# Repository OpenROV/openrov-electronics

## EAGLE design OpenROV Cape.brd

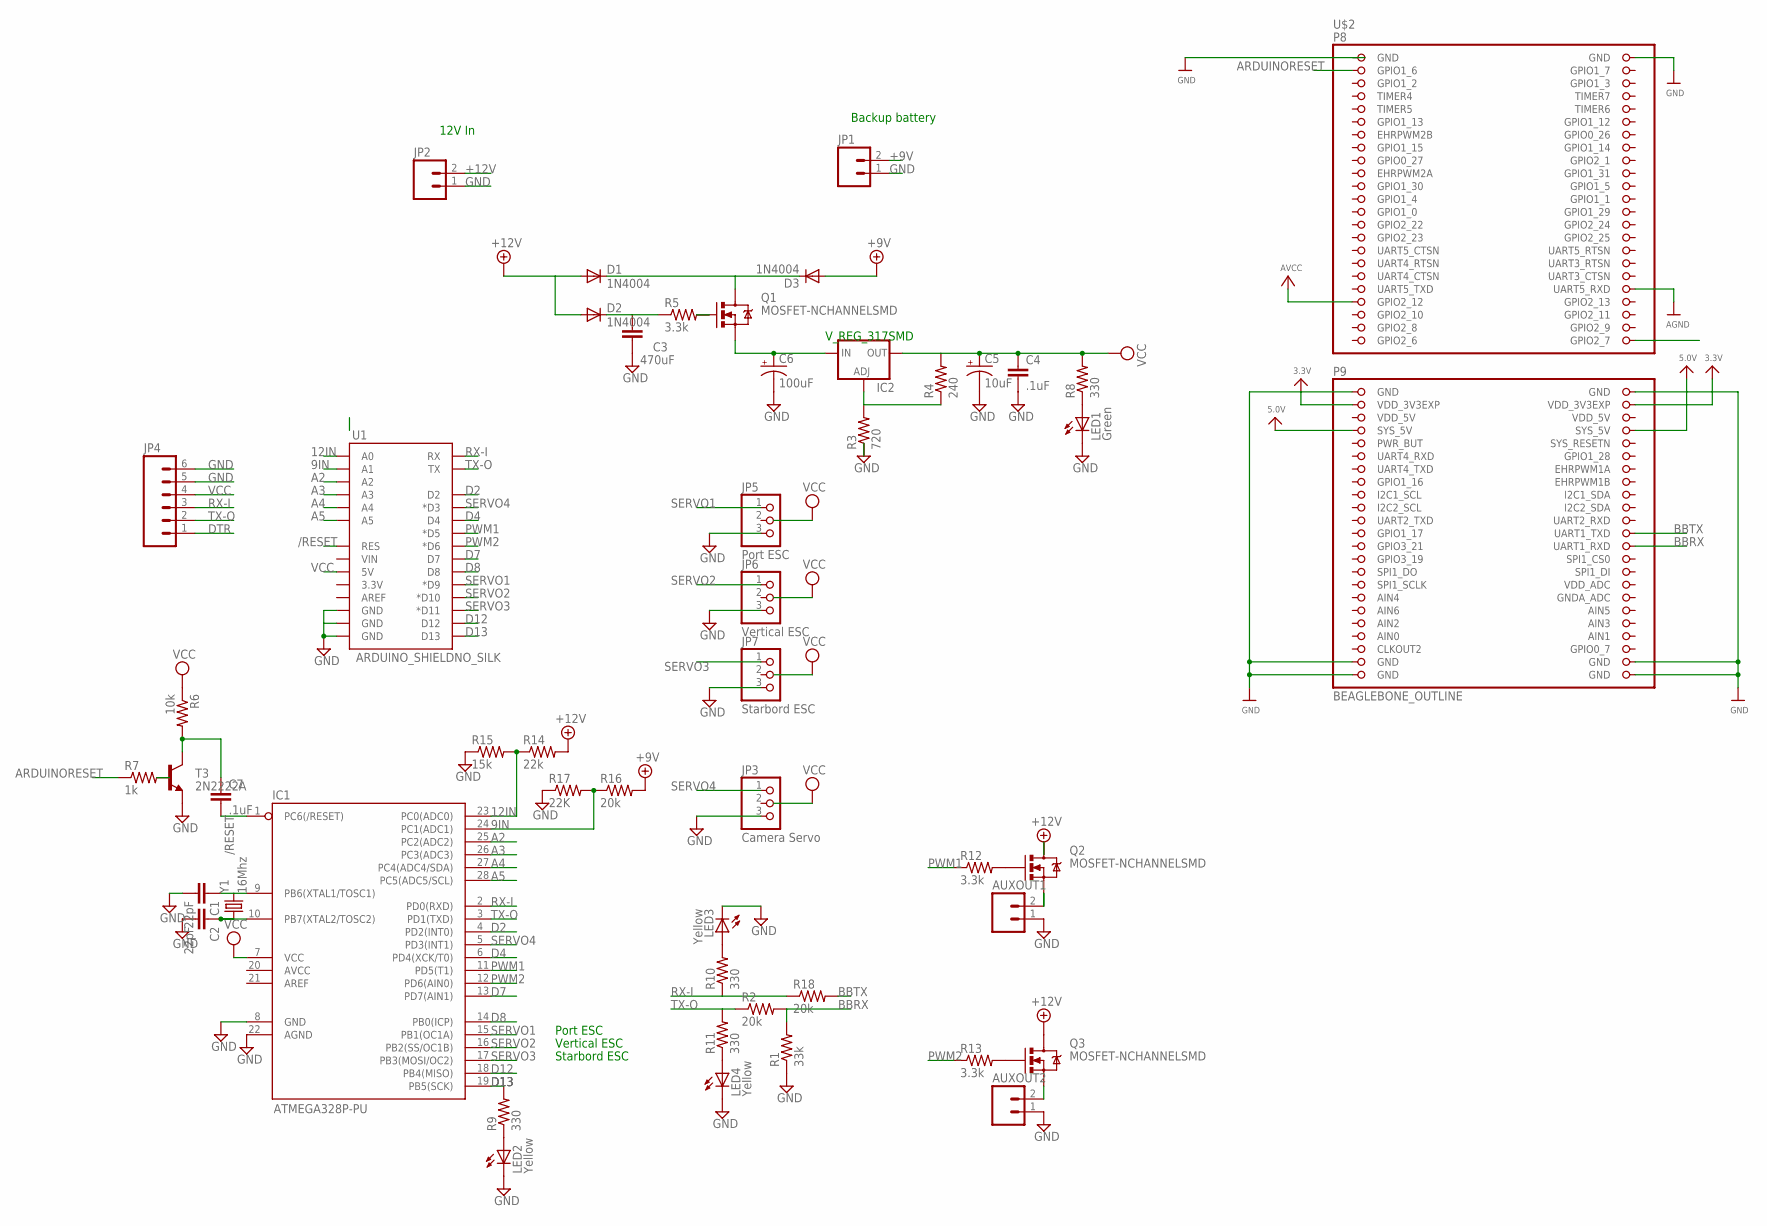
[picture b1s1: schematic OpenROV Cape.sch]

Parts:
AUXOUT1, AUXOUT2: M02PTH; 1X02
C1, C2: 22pF; 0805
C3: 470uF; 0805
C4, C7: .1uF; 0805
C5: 10uF; EIA3216
C6: 100uF; EIA3216
D1, D2, D3: 1N4004; SMA-DIODE
IC1: ATMEGA328P-PU; DIL28-3
IC2: V_REG_317SMD; SOT223
JP1, JP2: M02PTH; 1X02
JP3: Camera Servo; 1X03
JP4: M06SIP; 1X06
JP5: Port ESC; 1X03
JP6: Vertical ESC; 1X03
JP7: Starbord ESC; 1X03
LED1: Green; LED-1206
LED2, LED3, LED4: Yellow; LED-1206
Q1, Q2, Q3: MOSFET-NCHANNELSMD; SOT23-3
R1: 33k; 0805
R2, R16, R18: 20k; 0805
R3: 720; 0805
R4: 240; 0805
R5, R12, R13: 3.3k; 0805
R6: 10k; 0805
R7: 1k; 0805
R8, R9, R10, R11: 330; 0805
R14: 22k; 0805
R15: 15k; 0805
R17: 22K; 0805
T3: 2N2222A; SOT23
U1: ARDUINO_SHIELDNO_SILK; DUEMILANOVE_VIAS
U$2: BEAGLEBONE_OUTLINE; BEAGLEBONE_SHIELD
Y1: 16Mhz; HC49US

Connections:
3.3V: U$2.49 (VDD_3V3EXP), U$2.50 (VDD_3V3EXP)
5.0V: U$2.53 (SYS_5V), U$2.54 (SYS_5V)
9IN: IC1.24 (PC1(ADC1)), R16.1, R17.2, U1.A1
12IN: IC1.23 (PC0(ADC0)), R14.1, R15.2, U1.A0
+9V: D3.A, JP1.2, R16.2
+12V: D1.A, D2.A, JP2.2, Q2.3 (D), Q3.3 (D), R14.2
/RESET: C7.1, R6.2, T3.3 (C), U1.RES
A2: IC1.25 (PC2(ADC2)), U1.A2
A3: IC1.26 (PC3(ADC3)), U1.A3
A4: IC1.27 (PC4(ADC4/SDA)), U1.A4
A5: IC1.28 (PC5(ADC5/SCL)), U1.A5
AGND: U$2.38 (UART5_RXD)
AIN0: U$2.85 (AIN0)
AIN3: U$2.84 (AIN3)
ARDUINORESET: R7.1, U$2.3 (GPIO1_6)
AVCC: U$2.39 (GPIO2_12)
BBRX: R1.2, R2.2, U$2.72 (UART1_RXD)
BBTX: R18.2, U$2.70 (UART1_TXD)
D2: IC1.4 (PD2(INT0)), U1.D2
D4: IC1.6 (PD4(XCK/T0)), U1.D4
D7: IC1.13 (PD7(AIN1)), U1.D7
D8: IC1.14 (PB0(ICP)), U1.D8
D12: IC1.18 (PB4(MISO)), U1.D12
D13: IC1.19 (PB5(SCK)), R9.2, U1.D13
DTR: JP4.1
GND: AUXOUT1.1, AUXOUT2.1, C1.2, C2.2, C3.2, C4.2, C5.C (-), C6.C (-), IC1.22 (AGND), JP1.1, JP2.1, JP3.3, JP4.5, JP4.6, JP5.3, JP6.3, JP7.3, LED1.C, LED2.C, LED3.C, LED4.C, R1.1, R3.1, R15.1, R17.1, T3.2 (E), U1.GND@0 (GND), U1.GND@1 (GND), U1.GND@2 (GND), U$2.1 (GND), U$2.2 (GND), U$2.47 (GND), U$2.48 (GND), U$2.89 (GND), U$2.90 (GND), U$2.91 (GND), U$2.92 (GND)
GPIO1_7: U$2.4 (GPIO1_7)
GPIO2_6: U$2.45 (GPIO2_6)
GPIO2_8: U$2.43 (GPIO2_8)
GPIO2_9: U$2.44 (GPIO2_9)
GPIO2_11: U$2.42 (GPIO2_11)
unnamed: LED3.A, R10.2
unnamed: C7.2, IC1.1 (PC6(/RESET))
unnamed: R7.2, T3.1 (B)
unnamed: IC2.1 (ADJ), R3.2, R4.1
unnamed: LED1.A, R8.1
unnamed: LED2.A, R9.1
unnamed: LED4.A, R11.1
unnamed: AUXOUT1.2, Q2.2 (S)
unnamed: Q2.1 (G), R12.2
unnamed: AUXOUT2.2, Q3.2 (S)
unnamed: Q3.1 (G), R13.2
unnamed: C2.1, IC1.10 (PB7(XTAL2/TOSC2)), Y1.1
unnamed: C1.1, IC1.9 (PB6(XTAL1/TOSC1)), Y1.2
unnamed: C3.1, D2.C, R5.1
unnamed: Q1.1 (G), R5.2
unnamed: D1.C, D3.C, Q1.3 (D)
unnamed: C6.A (+), IC2.3 (IN), Q1.2 (S)
PWM1: IC1.11 (PD5(T1)), R12.1, U1.D5 (*D5)
PWM2: IC1.12 (PD6(AIN0)), R13.1, U1.D6 (*D6)
RX-I: IC1.2 (PD0(RXD)), JP4.3, R10.1, R18.1, U1.RX
SERVO1: IC1.15 (PB1(OC1A)), JP5.1, U1.D9 (*D9)
SERVO2: IC1.16 (PB2(SS/OC1B)), JP6.1, U1.D10 (*D10)
SERVO3: IC1.17 (PB3(MOSI/OC2)), JP7.1, U1.D11 (*D11)
SERVO4: IC1.5 (PD3(INT1)), JP3.1, U1.D3 (*D3)
TX-O: IC1.3 (PD1(TXD)), JP4.2, R2.1, R11.2, U1.TX
VCC: C4.1, C5.A (+), IC1.7 (VCC), IC2.2 (OUT), JP4.4, R4.2, R6.1, R8.2, U1.5V
VDD_5V: U$2.51 (VDD_5V), U$2.52 (VDD_5V)

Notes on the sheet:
Port ESC
Vertical ESC
Starbord ESC
Backup battery
12V In
V_REG_317SMD

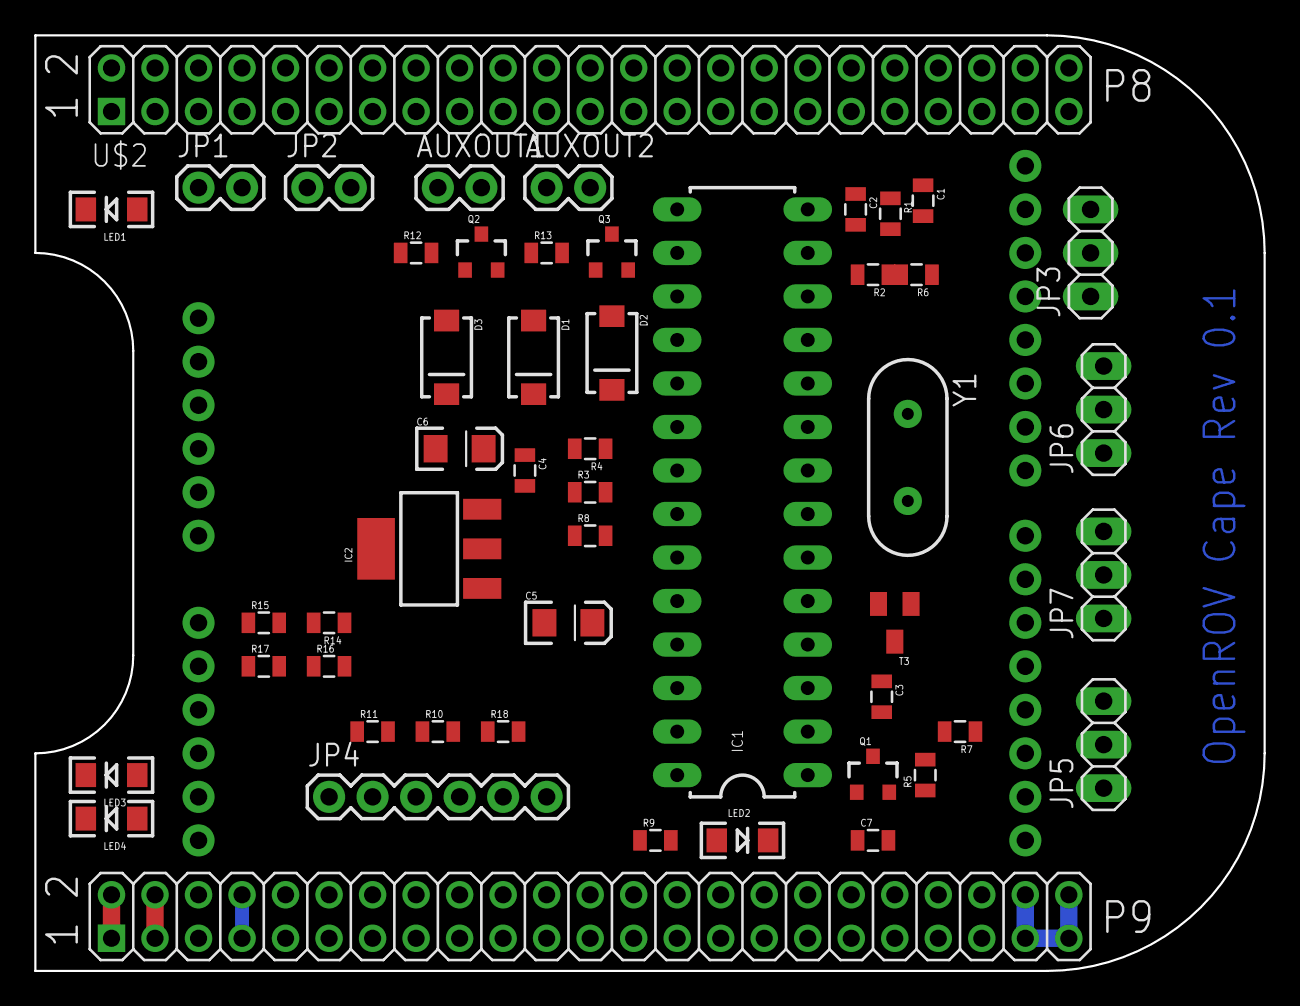
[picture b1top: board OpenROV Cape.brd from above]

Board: 2 copper layers, 71.8 x 54.6 mm, 50 parts (0 on the bottom side), 48 nets.

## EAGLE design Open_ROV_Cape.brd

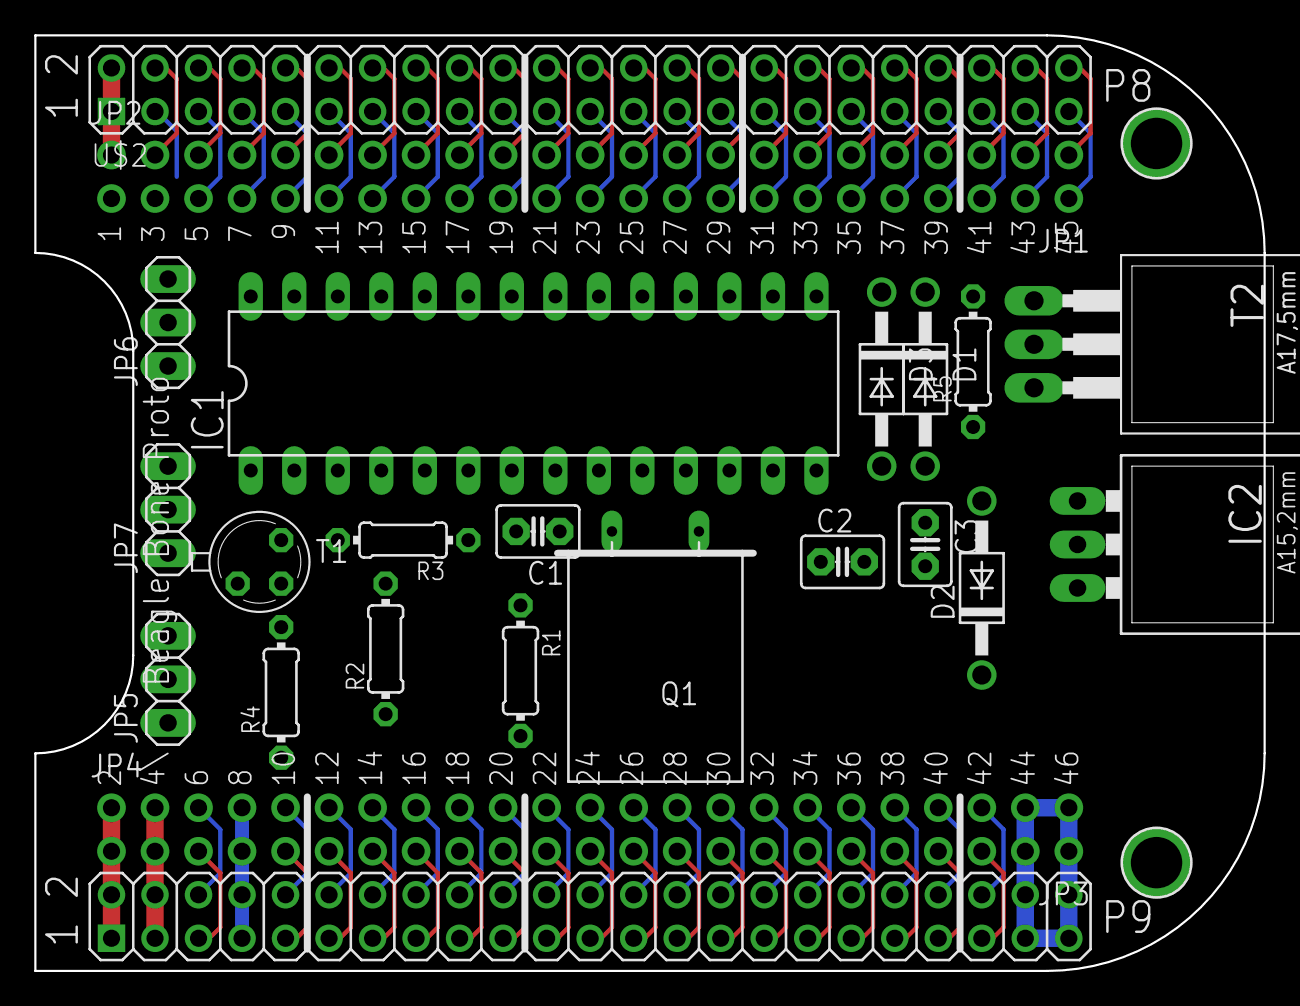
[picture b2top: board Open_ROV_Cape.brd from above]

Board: 2 copper layers, 71.8 x 54.6 mm, 26 parts (0 on the bottom side), 95 nets.

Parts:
C1, C2, C3: C2.5-3
D1, D2, D3: 1N4004; DO41-10
IC1: DIL28-4
IC2: 78XXL
JP1, JP2, JP3, JP4: 1X23_ROUND_70MIL
JP5, JP6, JP7: 1X03
Q1: Q
R1, R2, R3, R4, R5: 0204/7
T1: 2N2222; TO18
T2: TIP122; TO220
U$2: BEAGLEBONE_OUTLINE; BEAGLEBONE_SHIELD
U$22, U$23: MOUNTINGHOLE3.0THIN; MOUNTINGHOLE_3.0_PLATEDTHIN

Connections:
3.3V: JP3.22, JP4.2, U$2.49, U$2.50
5.0V: JP3.20, JP4.4, U$2.53, U$2.54
+12V: D1.A, D2.A
AGND: JP2.19, U$2.38
AVCC: JP1.4, U$2.39
GND: C1.2, C2.2, C3.2, IC1.8, IC1.22, IC2.GND, JP1.23, JP2.1, JP3.1, JP3.2, JP3.23, JP4.1, JP4.22, JP4.23, JP5.3, JP6.3, JP7.3, R1.1, T1.1, U$2.1, U$2.2, U$2.47, U$2.48, U$2.89, U$2.90, U$2.91, U$2.92
unnamed: IC1.1, R3.2, T1.3
unnamed: R4.2, T1.2
unnamed: JP1.20, U$2.7
unnamed: JP1.19, U$2.9
unnamed: JP1.18, U$2.11
unnamed: JP1.17, U$2.13
unnamed: JP1.16, U$2.15
unnamed: JP1.15, U$2.17
unnamed: JP1.14, U$2.19
unnamed: JP1.13, U$2.21
unnamed: JP1.12, U$2.23
unnamed: JP1.11, U$2.25
unnamed: JP1.10, U$2.27
unnamed: JP1.9, U$2.29
unnamed: JP1.8, U$2.31
unnamed: JP1.7, U$2.33
unnamed: JP1.6, U$2.35
unnamed: JP1.5, U$2.37
unnamed: JP1.3, U$2.41
unnamed: JP1.2, U$2.43
unnamed: JP1.1, U$2.45
unnamed: C2.1, IC1.10, Q1.1
unnamed: C1.1, IC1.9, Q1.2
unnamed: JP2.4, U$2.8
unnamed: JP2.5, U$2.10
unnamed: JP2.6, U$2.12
unnamed: JP2.7, U$2.14
unnamed: JP2.8, U$2.16
unnamed: JP2.9, U$2.18
unnamed: JP2.10, U$2.20
unnamed: JP2.11, U$2.22
unnamed: JP2.12, U$2.24
unnamed: JP2.13, U$2.26
unnamed: JP2.14, U$2.28
unnamed: JP2.15, U$2.30
unnamed: JP2.16, U$2.32
unnamed: JP2.17, U$2.34
unnamed: JP2.18, U$2.36
unnamed: JP2.20, U$2.40
unnamed: JP2.21, U$2.42
unnamed: JP2.22, U$2.44
unnamed: JP2.23, U$2.46
unnamed: JP1.22, U$2.3
unnamed: JP1.21, U$2.5
unnamed: JP3.21, U$2.51
unnamed: JP2.2, U$2.4
unnamed: JP3.19, U$2.55
unnamed: JP3.18, U$2.57
unnamed: JP3.17, U$2.59
unnamed: JP3.16, U$2.61
unnamed: JP3.15, U$2.63
unnamed: JP3.14, U$2.65
unnamed: JP3.13, U$2.67
unnamed: JP3.12, U$2.69
unnamed: JP3.11, U$2.71
unnamed: JP3.10, U$2.73
unnamed: JP3.9, U$2.75
unnamed: JP3.8, U$2.77
unnamed: JP3.7, U$2.79
unnamed: JP3.6, U$2.81
unnamed: JP3.5, U$2.83
unnamed: JP3.4, U$2.85
unnamed: JP3.3, U$2.87
unnamed: JP2.3, U$2.6
unnamed: JP4.21, U$2.88
unnamed: C3.1, D2.C, R5.1
unnamed: JP4.3, U$2.52
unnamed: R5.2, T2.1
unnamed: JP4.5, U$2.56
unnamed: JP4.6, U$2.58
unnamed: JP4.7, U$2.60
unnamed: JP4.8, U$2.62
unnamed: JP4.9, U$2.64
unnamed: JP4.10, U$2.66
unnamed: JP4.11, U$2.68
unnamed: JP4.12, U$2.70
unnamed: JP4.13, U$2.72
unnamed: JP4.14, U$2.74
unnamed: JP4.15, U$2.76
unnamed: JP4.16, U$2.78
unnamed: JP4.17, U$2.80
unnamed: JP4.18, U$2.82
unnamed: JP4.19, U$2.84
unnamed: JP4.20, U$2.86
unnamed: D1.C, D3.C, T2.2
unnamed: IC2.IN, T2.3
unnamed: R1.2, R2.1
unnamed: IC1.3, R2.2
VCC: IC1.7, IC2.OUT, R3.1

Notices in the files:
parts and their libraries:
SparkFun: Licensing: CC v3.0 Share-Alike You are welcome to use this library for commercial purposes.
